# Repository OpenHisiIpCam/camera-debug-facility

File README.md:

# camera-debug-facility

Hands free remote embedded development device.

End user documentation is hosted at https://www.openhisiipcam.org/camera-debug-facility.

## Overview schema

## Schematics

Can be found in `hardware/cdf-1`.

## Prototype

## Features

### Control interfaces
* FastEthernet
* WiFi (ap or client)
* http api
* uart via telnet
* uart via websockets
* spi flash programmer
* tftp server

### Dut control
* power via gpiod relay
* uart
* spi flash mem
* FastEthernet

## Implementation

### Proposed deploy schema

squashfs rootfs to ram
jffs2 user via overlay

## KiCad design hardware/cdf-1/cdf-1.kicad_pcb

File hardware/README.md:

# Hardware 

* `adapters` - collection of adapters
* `arduino-muxed-programmer` - Muxed SPI serprog programmer, shield for Arduino UNO.
* `cdf-1` - TODO

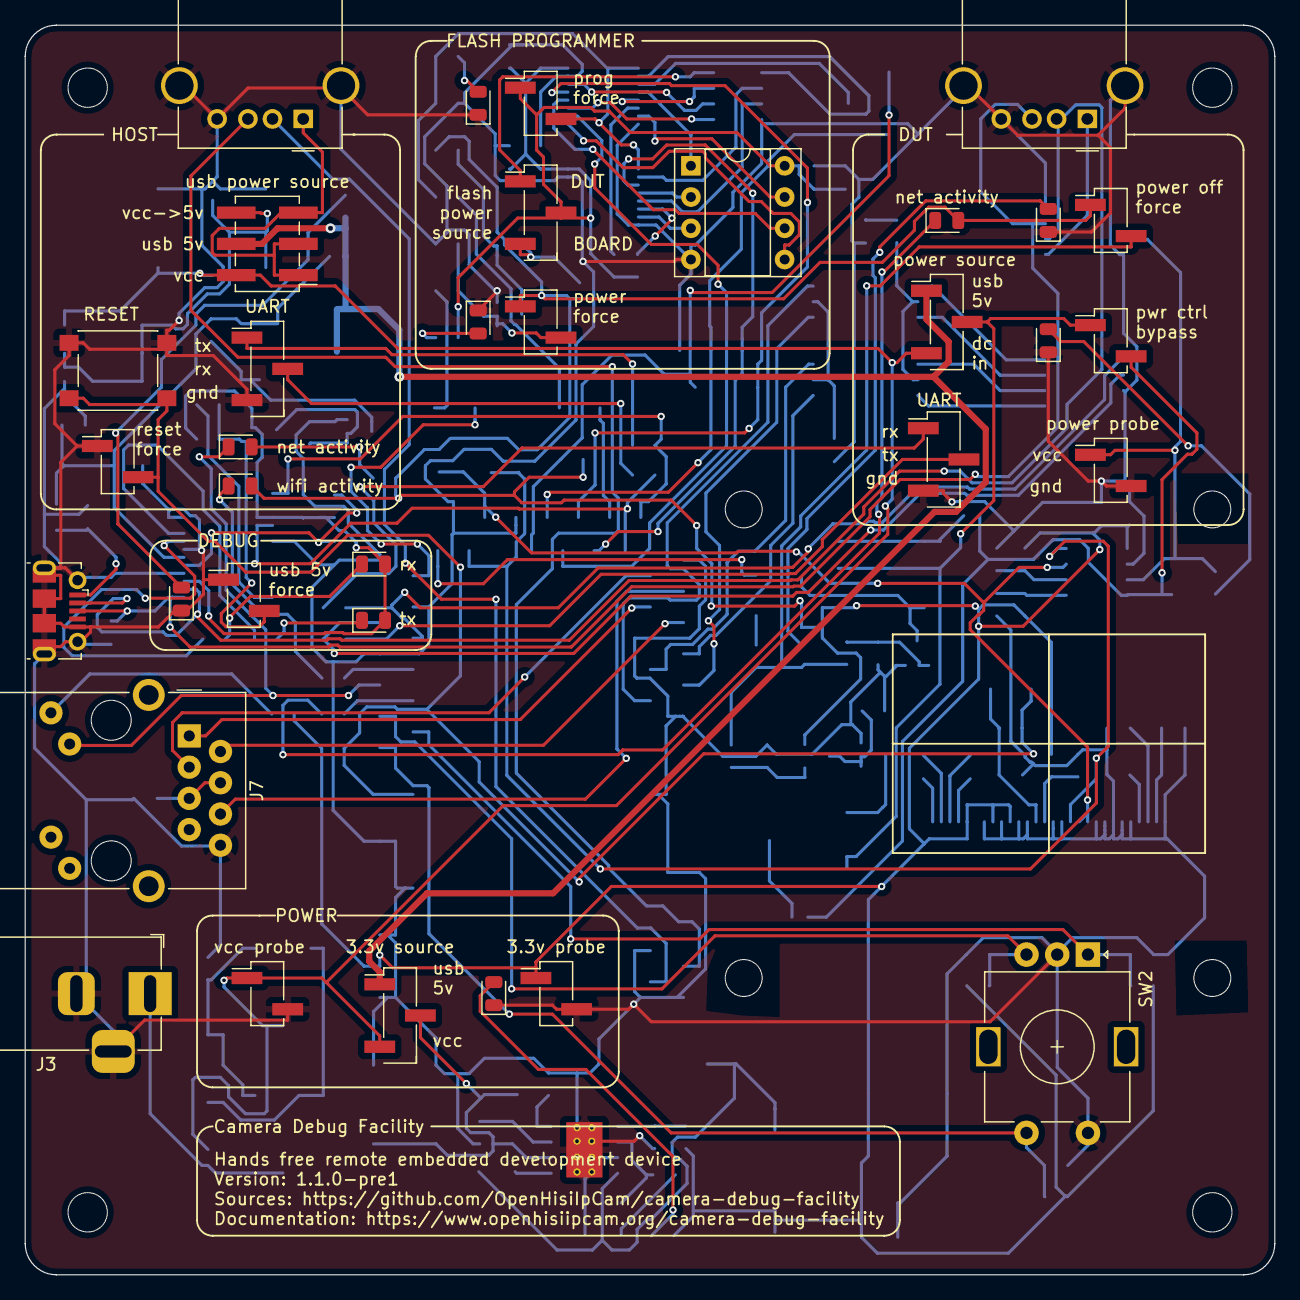
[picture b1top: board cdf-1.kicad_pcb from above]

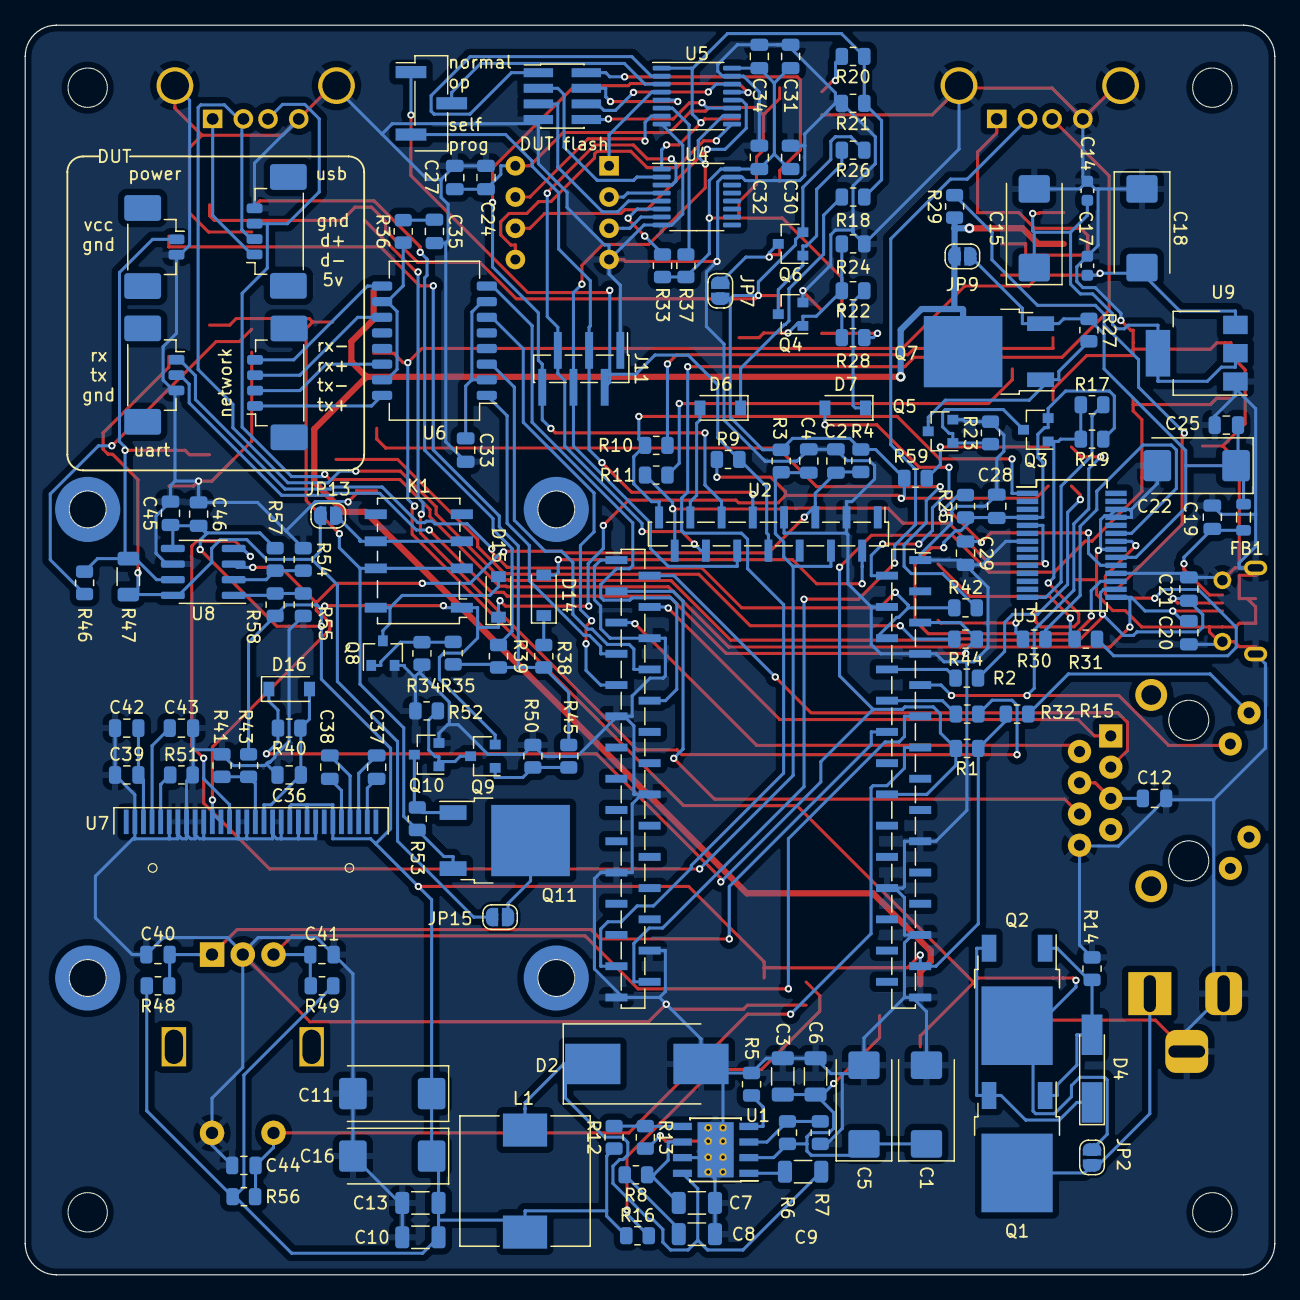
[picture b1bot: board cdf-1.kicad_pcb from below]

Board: 2 copper layers, 101.6 x 101.6 mm, 187 parts (149 on the bottom side), 131 nets.

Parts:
C1, C5, C11, C15, C16, C18, C22: CP; CP_EIA-7343-31_Kemet-D_Pad2.25x2.55mm_HandSolder
C2, C4, C12, C19, C20, C21, C24, C25, C27, C28, C29, C30, C31, C32, C33, C34, C35, C36, C39, C40, C41, C42, C43, C44, C45, C46: C; C_0805_2012Metric
C3, C6, C7, C8, C9, C10, C13: C; C_1206_3216Metric
C14, C17: C; C_0603_1608Metric
C37, C38: CP; C_0805_2012Metric
D1: WIFI LED; LED_0805_2012Metric
D2: D_Schottky; D_SMC_Handsoldering
D3: 3.3V POWER LED; LED_0805_2012Metric
D4: D_Zener; D_MiniMELF_Handsoldering
D5: MUX PROG LED; LED_0805_2012Metric
D6, D7, D14: D_Schottky; D_SOD-123
D8: SPI PWR; LED_0805_2012Metric
D9: USB POWER CTRL LED; LED_0805_2012Metric
D10: TX; LED_0805_2012Metric
D11: RX; LED_0805_2012Metric
D12: DUT ETH LED; LED_0805_2012Metric
D13: DUT POWER CTRL LED; LED_0805_2012Metric
D15, D16: D; D_SOD-123
D17: DUT PWR LED; LED_0805_2012Metric
D18: WAN LED; LED_0805_2012Metric
FB1: Ferrite_Bead; L_0805_2012Metric
H1, H2, H3, H4: MOUNT; Mounting_Wuerth_WA-SMSI-M2_H2mm_9774020243
H5, H6, H7, H8: 3mm HOLE; MountingHole_3.2mm_M3
J1: USB_B_Micro; USB_Micro-B_Molex-105017-0001
J3: DUT DC POWER IN; BarrelJack_Horizontal
J4: DEBUG UART PROBE; PinHeader_1x03_P2.54mm_Vertical_SMD_Pin1Left
J5: VCC PROBE; PinHeader_1x02_P2.54mm_Vertical_SMD_Pin1Left
J6: MT7688 USB HOST; USB_A_Molex_67643_Horizontal
J7: WAN; RJ45_Amphenol_RJMG1BD3B8K1ANR
J10: SPI FLASH DIP; DIP-8_W7.62mm_Socket
J11: SPI PROBE; PinHeader_1x06_P1.27mm_Vertical_SMD_Pin1Left
J12: DUT SPI FLASH; PinHeader_2x04_P1.27mm_Vertical_SMD
J13: 3v3 probe; PinHeader_1x02_P2.54mm_Vertical_SMD_Pin1Left
J14: DUT FETH T; Molex_PicoBlade_53398-0471_1x04-1MP_P1.25mm_Vertical
J15: DUT UART PROBE; PinHeader_1x03_P2.54mm_Vertical_SMD_Pin1Left
J16: DUT UART; Molex_PicoBlade_53398-0371_1x03-1MP_P1.25mm_Vertical
J17: DUT USB PORT; USB_A_Molex_67643_Horizontal
J18: DUT POWER; Molex_PicoBlade_53398-0271_1x02-1MP_P1.25mm_Vertical
J19: DUT USB; Molex_PicoBlade_53398-0471_1x04-1MP_P1.25mm_Vertical
J20: DUT POWER2; PinHeader_1x02_P2.54mm_Vertical_SMD_Pin1Left
JP1: 3.3V SOURCE; PinHeader_1x03_P2.54mm_Vertical_SMD_Pin1Left
JP2: REVERSE POL PROTECTION BYPASS; SolderJumper-2_P1.3mm_Open_RoundedPad1.0x1.5mm
JP3: FORCE RESET; PinHeader_1x02_P2.54mm_Vertical_SMD_Pin1Left
JP4: FORCE USB POWER; PinHeader_1x02_P2.54mm_Vertical_SMD_Pin1Left
JP5: FORCE 3V3 MUX; PinHeader_1x02_P2.54mm_Vertical_SMD_Pin1Left
JP6: FORCE PROG; PinHeader_1x02_P2.54mm_Vertical_SMD_Pin1Left
JP7: 3V3 CONTROL BYPASS; SolderJumper-2_P1.3mm_Open_RoundedPad1.0x1.5mm
JP8: DUT SPI FLASH PW SELECTOR; PinHeader_1x03_P2.54mm_Vertical_SMD_Pin1Left
JP9: VBUS CONTROL BYPASS; SolderJumper-2_P1.3mm_Open_RoundedPad1.0x1.5mm
JP10: SELF PROG; PinHeader_1x03_P2.54mm_Vertical_SMD_Pin1Left
JP11: DUT POWER SELECT; PinHeader_1x03_P2.54mm_Vertical_SMD_Pin1Left
JP12: DUT POWER OFF FORCE; PinHeader_1x02_P2.54mm_Vertical_SMD_Pin1Left
JP13: RELAY; SolderJumper-2_P1.3mm_Open_RoundedPad1.0x1.5mm
JP14: DUT POWER CONTROL BYPASS; PinHeader_1x02_P2.54mm_Vertical_SMD_Pin1Left
JP15: MOSFET; SolderJumper-2_P1.3mm_Open_RoundedPad1.0x1.5mm
JP16: VBUS SRC; PinHeader_2x03_P2.54mm_Vertical_SMD
K1: G6K-2; Relay_DPDT_Omron_G6K-2F-Y
L1: L; L_10.4x10.4_H4.8
Q1, Q2, Q7, Q11: AUIRFR5305; TO-252-2
Q3, Q6, Q9: IRLML6402; SOT-23
Q4, Q5, Q10: BSS138; SOT-23
Q8: BC847; SOT-23
R1, R2, R3, R4, R5, R6, R7, R8, R9, R10, R11, R12, R13, R14, R15, R16, R17, R18, R19, R20, R21, R22, R23, R24, R25, R26, R27, R28, R29, R30, R31, R32, R33, R34, R35, R37, R38, R39, R40, R41, R42, R43, R44, R45, R46, R48, R49, R50, R51, R52, R53, R54, R55, R56, R57, R58, R59: R; R_0805_2012Metric
R36: 75; R_0805_2012Metric
R47: 0.1; R_1206_3216Metric
SW1: RESET; SW_Push_1P1T_NO_6x6mm_H9.5mm
SW2: Encoder; RotaryEncoder_Alps_EC11E-Switch_Vertical_H20mm
U1: TPS54360DDA; TI_SO-PowerPAD-8_ThermalVias
U2: JS76x8
U3: FT232RL; SSOP-28_5.3x10.2mm_P0.65mm
U4, U5: SN74CB3Q3257; TSSOP-16_4.4x5mm_P0.65mm
U6: EPCOS_A8065; Transformer_Pulse_H1100NL
U7: oled display(ssd1306); OLED-128O064D
U8: INA219AxD; SOIC-8_3.9x4.9mm_P1.27mm
U9: LM1117-5.0; SOT-223-3_TabPin2

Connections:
+3V3: C10.1, C11.1, C13.1, C16.1, C45.1, C46.2, D1.2 (A), D12.2 (A), D15.1 (K), J13.1, JP5.1 (A), JP7.1 (A), JP12.1 (A), K1.1, L1.2, Q6.2 (S), Q9.2 (S), R1.1, R3.1, R4.2, R9.1, R12.1, R15.1, R16.1, R26.1, R43.1, R48.2, R49.1, R56.1, R57.1, R58.1, R59.1, U2.3 (VDD3V3), U7.6 (VBAT), U7.9 (VDD), U7.11 (BS1), U8.5 (VS)
+5V: JP1.1 (A), JP9.2 (B), JP11.1 (A), JP16.4, Q7.2 (D), R29.1
/DUSB_N: C21.1, J1.2 (D-), J17.2 (D-), J19.2, U3.16 (USBD-)
/DUSB_P: C20.1, J1.3 (D+), J17.3 (D+), J19.3, U3.15 (USBD+)
/DUT_T_ETH_R_N: J14.4, U6.9 (RX-)
/DUT_T_ETH_R_P: J14.3, U6.11 (RX+)
/DUT_T_ETH_T_N: J14.2, U6.14 (TX-)
/DUT_T_ETH_T_P: J14.1, U6.16 (TX+)
/H_USB_N: J6.2 (D-), U2.72 (USB_N)
/H_USB_P: J6.3 (D+), U2.71 (USB_P)
/WAN_R_N: J7.R6 (RD-), U2.47 (MDI_R_P0_N)
/WAN_R_P: J7.R3 (RD+), U2.46 (MDI_R_P0_P)
/WAN_T_N: J7.R2 (TD-), U2.49 (MDI_T_P0_N)
/WAN_T_P: J7.R1 (TD+), U2.48 (MDI_T_P0_P)
DUT_ETH_LED: R32.1, U2.20 (EPHY_LED1_N_JTDI)
DUT_ETH_R_N: U2.54 (MDI_R_P1_N), U6.8 (RD-)
DUT_ETH_R_P: U2.53 (MDI_R_P1_P), U6.6 (RD+)
DUT_ETH_T_N: U2.52 (MDI_T_P1_N), U6.3 (TD-)
DUT_ETH_T_P: U2.51 (MDI_T_P1_P), U6.1 (TD+)
DUT_POWER_CONTROL: D14.2 (A), U2.31 (I2S_CLK)
DUT_SPI_CS: J12.1, U5.2 (1B1)
DUT_SPI_HOLD: J12.4, U5.5 (2B1)
DUT_SPI_MISO: J12.3, U4.2 (1B1)
DUT_SPI_MOSI: J12.8, U5.11 (3B1)
DUT_SPI_SCK: J12.6, U5.14 (4B1)
DUT_SPI_VCC: J12.2, JP8.1 (A)
DUT_SPI_WP: J12.5, U4.5 (2B1)
GND: C1.2, C2.1, C3.2, C4.2, C5.2, C6.2, C7.2, C8.2, C10.2, C11.2, C12.2, C13.2, C14.2, C15.2, C16.2, C17.1, C18.1, C19.1, C20.2, C21.2, C22.2, C24.1, C25.1, C27.1, C28.1, C29.2, C30.2, C31.2, C32.2, C33.2, C34.2, C35.2, C36.2, C39.1, C40.1, C41.2, C42.1, C43.2, C44.1, C45.2, C46.1, D2.2 (A), D3.1 (K), D5.1 (K), D8.1 (K), D9.1 (K), D13.1 (K), D17.1 (K), J1.5 (GND), J1.6 (Shield), J3.2, J3.3, J4.3, J5.2, J6.4 (GND), J6.5 (Shield), J7.R8 (CHS_GROUND), J10.4, J11.1, J12.7, J13.2, J15.3, J16.3, J17.4 (GND), J17.5 (Shield), J18.2, J19.4, J20.2, JP3.1 (A), JP4.1 (A), Q4.2 (S), Q5.2 (S), Q8.2 (E), Q10.2 (S), R5.2, R7.1, R13.2, R14.2, R21.2, R23.2, R24.2, R34.1, R41.2, R50.2, R51.2, R52.2, R54.2, R55.2, SW1.1, SW2.C, SW2.S2, U1.7 (GND), U1.9 (GNDPAD), U2.1 (GND), U2.5 (GND), U2.8 (GND), U2.11 (GND), U2.23 (GND), U2.26 (GND), U2.29 (GND), U2.32 (GND), U2.36 (GND), U2.45 (GND), U2.50 (GND), U2.55 (GND), U2.60 (GND), U2.65 (GND), U2.70 (GND), U2.73 (GND), U3.7 (GND), U3.18 (GND), U3.21 (GND), U3.25 (AGND), U3.26 (TEST), U4.8 (GND), U4.15 (/OE), U5.8 (GND), U5.15 (/OE), U7.8 (VSS), U7.10 (BS0), U7.12 (BS2), U7.13 (CS#), U7.16 (R/W#), U7.17 (E/RS#), U7.21 (D3), U7.22 (D4), U7.23 (D5), U7.24 (D6), U7.25 (D7), U7.29 (VLSS), U8.6 (GND), U9.1 (GND)
I2C_SCL: C4.1, R3.2, U2.33 (I2C_SCLK), U7.18 (D0), U8.4 (SCL)
I2C_SDA: C2.2, R4.1, U2.34 (I2C_SD), U7.19 (D1), U7.20 (D2), U8.3 (SDA)
unnamed: C1.1, C3.1, C5.1, C6.1, JP1.2 (C), R6.2, U1.2 (VIN)
unnamed: C7.1, R8.1, U1.6 (COMP)
unnamed: C8.1, R8.2
unnamed: C9.1, D2.1 (K), L1.1, U1.8 (SW)
unnamed: C9.2, U1.1 (BOOT)
unnamed: C12.1, J7.R4 (CT), J7.R5 (CT)
unnamed: C14.1, C15.1, JP16.6, U9.2 (VO)
unnamed: C19.2, FB1.1, J1.1 (VBUS)
unnamed: C29.1, R25.2, U3.19 (~RESET)
unnamed: C33.1, U6.2 (CT), U6.7 (CT)
unnamed: C35.1, R36.2
unnamed: C36.1, D16.2 (A), R40.1, U7.14 (RES#)
unnamed: C37.1, U7.2 (C2P)
unnamed: C37.2, U7.3 (C2N)
unnamed: C38.1, U7.4 (C1P)
unnamed: C38.2, U7.5 (C2N)
unnamed: C39.2, C42.2, U7.28 (VCC)
unnamed: C43.1, U7.27 (VCOMH)
unnamed: D1.1 (K), R2.2
unnamed: D3.2 (A), R16.2
unnamed: D4.1 (K), Q1.3 (S), Q2.3 (S)
unnamed: D4.2 (A), Q1.1 (G), Q2.1 (G), R14.1
unnamed: D5.2 (A), R20.2
unnamed: D6.1 (K), R18.2
unnamed: D7.1 (K), R22.1
unnamed: D8.2 (A), R28.2
unnamed: D9.2 (A), R29.2
unnamed: D10.1 (K), R30.1
unnamed: D11.1 (K), R31.1
unnamed: D12.1 (K), R32.2
unnamed: D13.2 (A), R39.2
unnamed: D14.1 (K), R38.2
unnamed: D15.2 (A), K1.8, Q8.3 (C)
unnamed: D17.2 (A), R46.2
unnamed: D18.2 (A), R59.2
unnamed: J3.1, JP2.1 (A), Q1.2 (D)
unnamed: J4.1, R10.1
unnamed: J4.2, R11.1
unnamed: J6.1 (VBUS), JP16.1, JP16.3, JP16.5
unnamed: J7.L4, R15.2
unnamed: J15.1, R42.2
unnamed: J15.2, R44.2
unnamed: J17.1 (VBUS), J19.1
unnamed: J18.1, J20.1, R46.1, R47.2, U8.7 (IN-)
unnamed: JP4.2 (B), Q3.1 (G), R17.1, R19.2
unnamed: JP5.2 (B), Q4.1 (G), R22.2, R24.1
unnamed: JP7.2 (B), JP8.3 (B), Q6.3 (D)
unnamed: JP10.2 (C), U5.3 (1B2)
unnamed: JP11.2 (C), JP14.1 (A), K1.2, K1.7, Q11.3 (S), R53.1
unnamed: JP12.2 (B), R35.1, R38.1, R39.1, R45.2
unnamed: JP13.1 (A), K1.3, K1.6
unnamed: JP13.2 (B), JP14.2 (B), JP15.1 (A), R47.1, U8.8 (IN+)
unnamed: JP15.2 (B), Q11.2 (D)
unnamed: Q3.3 (D), Q5.1 (G), R23.1
unnamed: Q4.3 (D), Q6.1 (G), R26.2
unnamed: Q5.3 (D), Q7.1 (G), R27.2
unnamed: Q8.1 (B), R34.2, R35.2
unnamed: Q9.1 (G), R45.1, R50.1
unnamed: Q9.3 (D), Q10.1 (G), R52.1
unnamed: Q10.3 (D), Q11.1 (G), R53.2
unnamed: R2.1, U2.22 (WLED_N)
unnamed: R5.1, U1.4 (RT/CLK)
unnamed: R6.1, R7.2, U1.3 (EN)
unnamed: R12.2, R13.1, U1.5 (FB)
unnamed: R30.2, U3.23 (CBUS0)
unnamed: R31.2, U3.22 (CBUS1)
unnamed: R33.2, U4.6 (2B2)
unnamed: R36.1, U6.10 (CT), U6.15 (CT)
unnamed: R37.2, U5.6 (2B2)
unnamed: R41.1, R43.2, U7.15 (D/C#)
unnamed: R51.1, U7.26 (IREF)
unnamed: R54.1, R57.2, U8.2 (A0)
unnamed: R55.1, R58.2, U8.1 (A1)
PROG_SPI_CS0: J11.3, JP10.3 (B), U2.38 (SPI_CS0)
PROG_SPI_CS1: J11.2, JP10.1 (A), R9.2, U2.37 (SPI_CS1)
PROG_SPI_MISO: J11.5, U2.41 (SPI_MISO), U4.3 (1B2)
PROG_SPI_MOSI: J11.4, U2.39 (SPI_MOSI), U5.10 (3B2)
PROG_SPI_SCK: J11.6, U2.40 (SPI_CLK), U5.13 (4B2)
RESET: D16.1 (K), JP3.2 (B), R1.2, R40.2, SW1.2, U2.14 (PERST_N)
SPI_CS: J10.1, U5.4 (1A)
SPI_HOLD: J10.7, U5.7 (2A)
SPI_MISO: J10.2, U4.4 (1A)
SPI_MOSI: J10.5, U5.9 (3A)
SPI_MUXER_3V3_CONTROL: D7.2 (A), U2.28 (I2S_WS)
SPI_MUX_CONTROL: D6.2 (A), U2.42 (GPIO11)
SPI_MUX_CONTROL_P: JP6.2 (B), R18.1, R20.1, R21.1, U4.1 (Select), U5.1 (Select)
SPI_SCK: J10.6, U5.12 (4A)
SPI_VCC: C24.2, C27.2, C30.1, C31.1, C32.1, C34.1, J10.8, JP6.1 (A), JP8.2 (C), R28.1, R33.1, R37.1, U4.16 (VCC), U5.16 (VCC)
SPI_WP: J10.3, U4.7 (2A)
SW_BUTTON: C44.2, R56.2, SW2.S1, U2.17 (EPHY_LED4_N_JTRST_N)
SW_RA: C40.2, R48.1, SW2.A, U2.18 (EPHY_LED3_N_JTCLK)
SW_RB: C41.1, R49.2, SW2.B, U2.19 (EPHY_LED2_N_JTMS)
UART_DEBUG_RX: R10.2, U2.44 (UART_TXD0), U3.1 (TXD)
UART_DEBUG_TX: R11.2, U2.43 (UART_RXD0), U3.5 (RXD)
UART_DUT_N: J16.2, R44.1, U2.25 (UART_RXD1)
UART_DUT_P: J16.1, R42.1, U2.24 (UART_TXD1)
USB_PWREN: R17.2, U3.14 (CBUS3)
VBUS: C22.1, C25.2, FB1.2, JP9.1 (A), Q7.3 (S), R27.1, U3.20 (VCC)
VCC: C17.2, C18.2, J5.1, JP1.3 (B), JP2.2 (B), JP11.3 (B), JP16.2, Q2.2 (D), U9.3 (VI)
VCCIO: C28.2, D10.2 (A), D11.2 (A), Q3.2 (S), R19.1, R25.1, U3.4 (VCCIO), U3.17 (3V3OUT)
WAN_LED: D18.1 (K), J7.L3, U2.21 (EPHY_LED0_N_JTDO)

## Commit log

2021-09-12 initial sw
2021-09-13 pdfs
2021-09-15 arduino muxed programmer and adapters
2021-09-15 improve
2021-09-16 docs initial
2021-09-16 separate vendors
2021-09-16 release gh action
2021-09-18 minimal working system
2021-09-18 system env initial
2021-09-18 Update Makefile
2021-09-18 Deployed 1781b8a with MkDocs version: 1.2.2
2021-09-19 programmer speed test
2021-09-21 i2c tests
2021-09-22 gpio inputs
2021-10-09 1st prototype
2021-10-12 schematics 1.1.0
2021-10-25 PCB probe
